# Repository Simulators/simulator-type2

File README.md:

# The Type 2 Liverpool Ringing Simulator

In this repository you will find all the resources for building the Liverpool Ringing Simulator Project's Type 2 simulator interfaces and sensor heads, including:
* Hardware & Software Manuals
* Firmware Source Code
* KiCad PCB Designs
* PCB Fabrication Gerber Files

You probably want to start in the docs folder above...

Please note that this is a Build-it-Yourself project. No pre-built hardware is available.

The original (Type 1) Liverpool Simulator hardware and code can be found in the legacy repository at https://github.com/Simulators/simulator. The Type 1 simulator is no longer under active development.

If you didn't get here from https://www.simulators.org.uk/, you might want to go and look at that, too.

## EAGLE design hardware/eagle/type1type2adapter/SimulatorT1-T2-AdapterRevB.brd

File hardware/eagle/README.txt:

*** DEPRECATED ***

These CAD files are the last to be produced using Eagle prior to migration of PCB development to KiCad. These are provided for reference only, and are no longer maintained.

Please use the KiCad CAD files where possible.

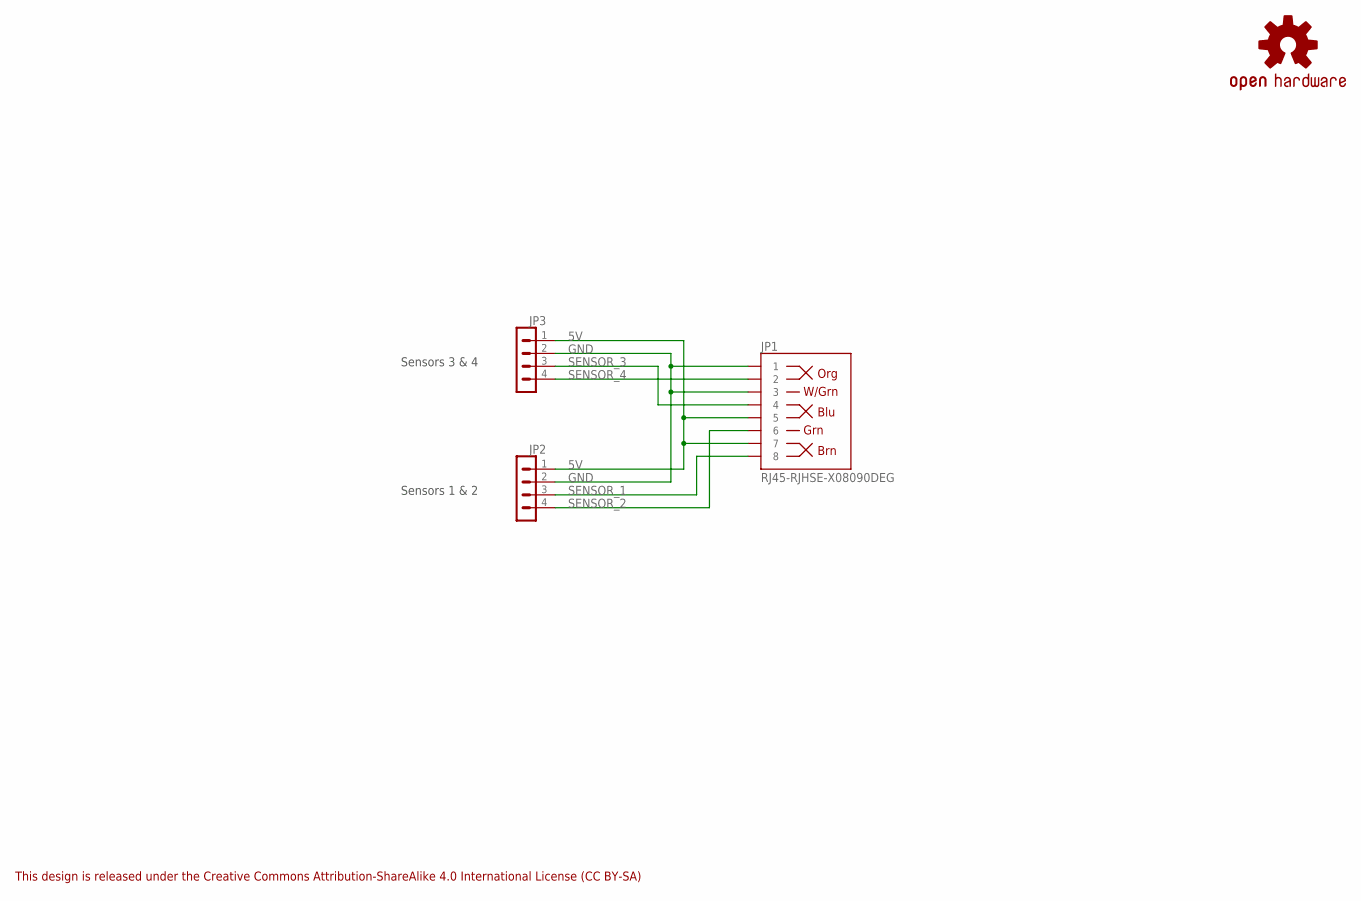
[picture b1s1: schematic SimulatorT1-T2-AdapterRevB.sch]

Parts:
JP1: RJ45-RJHSE-X08090DEG; RJ45-RJHSE-5080
JP2, JP3: MOLEX_KK_254_4WAY
LOGO1: OSHW-LOGOS; OSHW-LOGO-S

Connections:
5V: JP1.5, JP1.7, JP2.1, JP3.1
GND: JP1.1, JP1.3, JP2.2, JP3.2
SENSOR_1: JP1.8, JP2.3
SENSOR_2: JP1.6, JP2.4
SENSOR_3: JP1.4, JP3.3
SENSOR_4: JP1.2, JP3.4

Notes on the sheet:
This design is released under the Creative Commons Attribution-ShareAlike 4.0 International License (CC BY-SA)
Sensors 1 & 2
Sensors 3 & 4

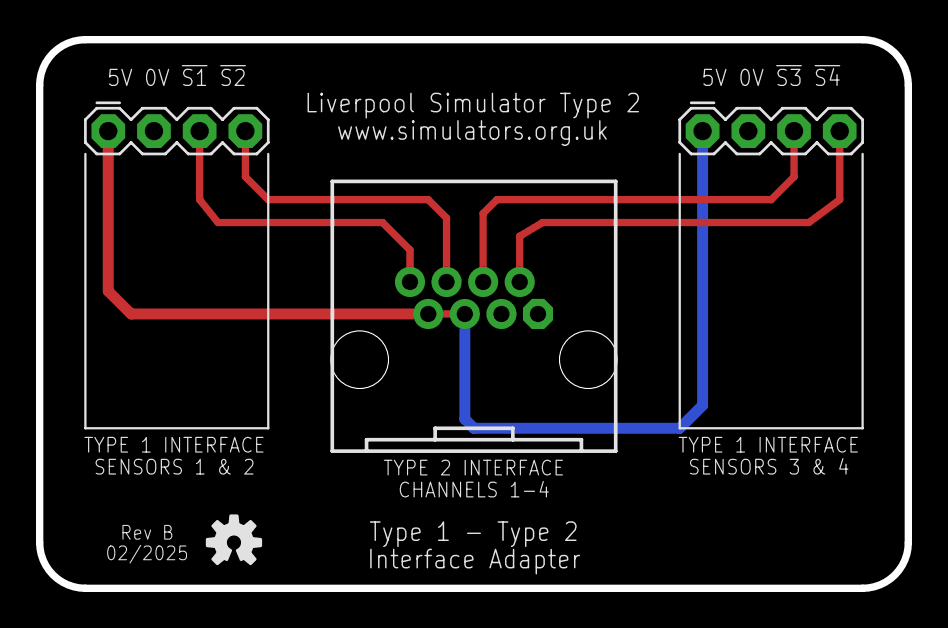
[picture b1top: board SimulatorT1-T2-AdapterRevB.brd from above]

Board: 2 copper layers, 48.3 x 30.5 mm, 5 parts (1 on the bottom side), 6 nets.

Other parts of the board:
U$1: WARNING_TRIANGLE_TPLACE

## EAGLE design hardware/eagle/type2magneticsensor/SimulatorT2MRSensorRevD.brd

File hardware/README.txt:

*** If you just want to order PCBs from a fabrication house, ready-made Gerber files can be found in the Gerbers directory ***

If you require PCB CAD files, please use those in the "kicad" subdirectory. The CAD files in the "eagle" subdirectory are the last to be produced using Eagle prior to migration of PCB development to KiCad. Those are provided for reference only, and are no longer maintained.

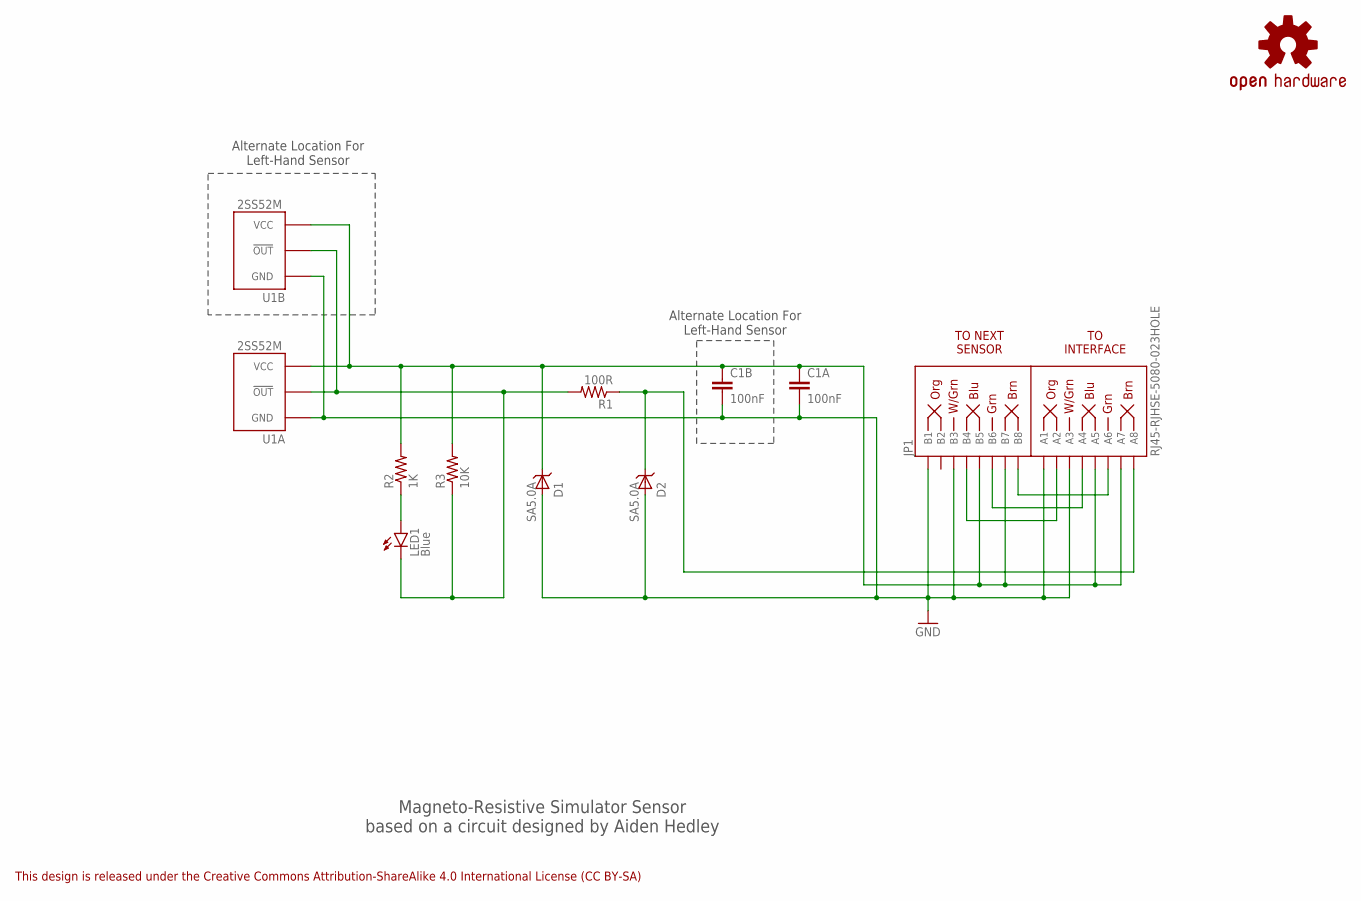
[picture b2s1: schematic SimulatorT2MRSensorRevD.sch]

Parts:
C1A, C1B: 100nF; CAP-PTH-SMALL
D1, D2: SA5.0A; DO41_TVS_UNI
JP1: RJ45-RJHSE-5080-023HOLE; RJ45-RJHSE-5080-02-3HOLE
LED1: Blue; LED3MM
LOGO1: OSHW-LOGOS; OSHW-LOGO-S
R1: 100R; AXIAL-0.4
R2: 1K; AXIAL-0.4
R3: 10K; AXIAL-0.4
U1A, U1B: 2SS52MOFFSET; 2SS52M_FLAT_OFFSET

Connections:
!OUT!: D2.CATHODE, JP1.A8, R1.P$1 (1)
B2: JP1.A6, JP1.B8
B3: JP1.A4, JP1.B6
B4: JP1.A2, JP1.B4
GND: C1A.2, C1B.2, D1.ANODE, D2.ANODE, JP1.A1, JP1.A3, JP1.B1, JP1.B3, U1A.P$1 (GND), U1B.P$1 (GND)
LED: LED1.A, R2.P$1 (1)
SIG: LED1.K (C), R1.P$2 (2), R3.P$1 (1), U1A.P$2 (!OUT!), U1B.P$2 (!OUT!)
VCC: C1A.1, C1B.1, D1.CATHODE, JP1.A5, JP1.A7, JP1.B5, JP1.B7, R2.P$2 (2), R3.P$2 (2), U1A.P$3 (VCC), U1B.P$3 (VCC)

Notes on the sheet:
This design is released under the Creative Commons Attribution-ShareAlike 4.0 International License (CC BY-SA)
TO INTERFACE
TO NEXT SENSOR
Magneto-Resistive Simulator Sensor based on a circuit designed by Aiden Hedley
Alternate Location For Left-Hand Sensor

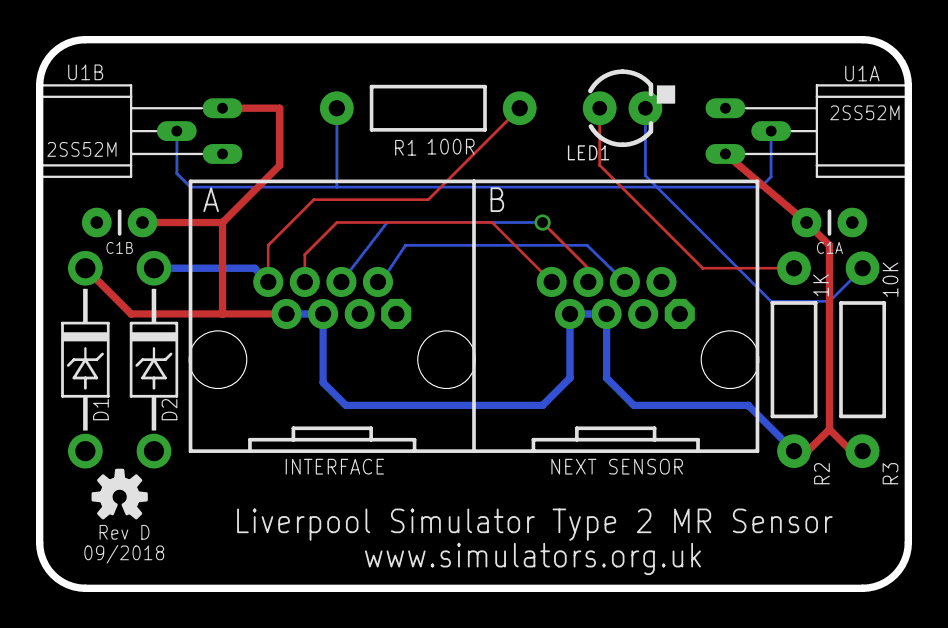
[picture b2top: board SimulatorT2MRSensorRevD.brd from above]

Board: 2 copper layers, 48.3 x 30.5 mm, 13 parts (1 on the bottom side), 8 nets.

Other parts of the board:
U$1: WARNING_TRIANGLE_TPLACE

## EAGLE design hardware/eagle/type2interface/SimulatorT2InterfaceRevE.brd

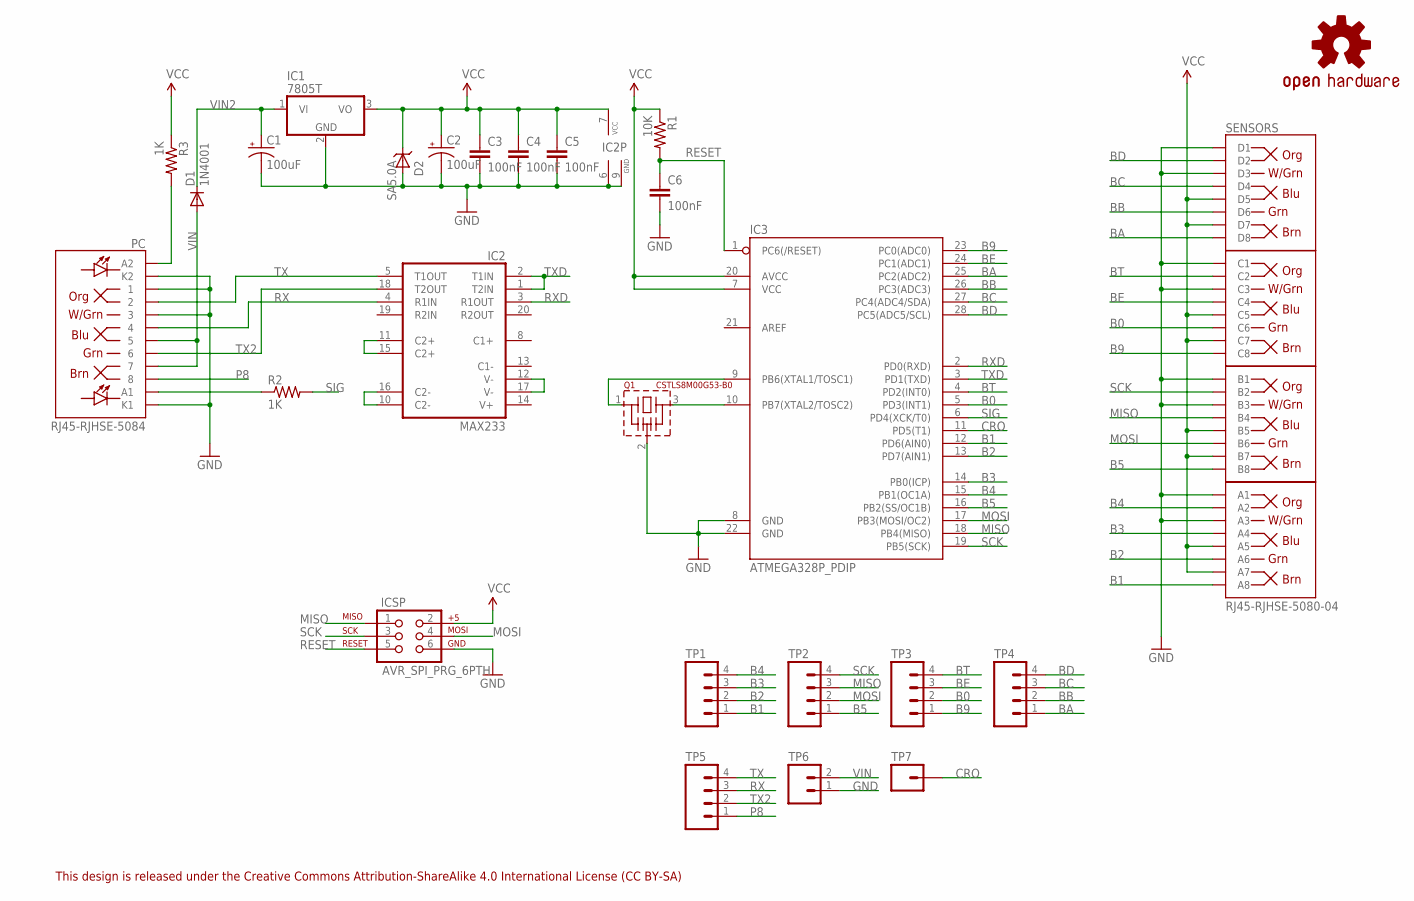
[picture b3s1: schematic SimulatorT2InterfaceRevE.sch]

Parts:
C1, C2: 100uF; CPOL-RADIAL-100UF-25V
C3, C4, C5, C6: 100nF; CAP-PTH-SMALL
D1: 1N4001; DO41_DIODE
D2: SA5.0A; DO41_TVS_UNI
IC1: 7805T; TO220H+TSR
IC2: MAX233; DIL20
IC3: ATMEGA328P_PDIP; DIL28-3
ICSP: AVR_SPI_PRG_6PTH; 2X3
LOGO1: OSHW-LOGOS; OSHW-LOGO-S
PC: RJ45-RJHSE-5084
Q1: CSTLS8M00G53-B0; CSTLS_G8
R1: 10K; AXIAL-0.4
R2, R3: 1K; AXIAL-0.4
SENSORS: RJ45-RJHSE-5080-04
TP1, TP2, TP3, TP4, TP5: M04PTH; 1X04
TP6: M02PTH; 1X02
TP7: M01PTH; 1X01

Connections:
B0: IC3.5 (PD3(INT1)), SENSORS.C6, TP3.2
B1: IC3.12 (PD6(AIN0)), SENSORS.A8, TP1.1
B2: IC3.13 (PD7(AIN1)), SENSORS.A6, TP1.2
B3: IC3.14 (PB0(ICP)), SENSORS.A4, TP1.3
B4: IC3.15 (PB1(OC1A)), SENSORS.A2, TP1.4
B5: IC3.16 (PB2(SS/OC1B)), SENSORS.B8, TP2.1
B9: IC3.23 (PC0(ADC0)), SENSORS.C8, TP3.1
BA: IC3.25 (PC2(ADC2)), SENSORS.D8, TP4.1
BB: IC3.26 (PC3(ADC3)), SENSORS.D6, TP4.2
BC: IC3.27 (PC4(ADC4/SDA)), SENSORS.D4, TP4.3
BD: IC3.28 (PC5(ADC5/SCL)), SENSORS.D2, TP4.4
BE: IC3.24 (PC1(ADC1)), SENSORS.C4, TP3.3
BT: IC3.4 (PD2(INT0)), SENSORS.C2, TP3.4
CRO: IC3.11 (PD5(T1)), TP7.1
GND: C1.2 (-), C2.2 (-), C3.2, C4.2, C5.2, C6.2, D2.ANODE, IC1.2 (GND), IC2.6 (GND), IC2.9 (GND), IC3.8 (GND), IC3.22 (GND), ICSP.6, PC.1, PC.3, PC.K1, PC.K2, Q1.2 (GND), SENSORS.A1, SENSORS.A3, SENSORS.B1, SENSORS.B3, SENSORS.C1, SENSORS.C3, SENSORS.D1, SENSORS.D3, TP6.1
LED1: PC.A1, R2.P$1 (1)
LED2: PC.A2, R3.P$2 (2)
MISO: IC3.18 (PB4(MISO)), ICSP.1, SENSORS.B4, TP2.3
MOSI: IC3.17 (PB3(MOSI/OC2)), ICSP.4, SENSORS.B6, TP2.2
unnamed: IC2.10 (C2-), IC2.16 (C2-)
unnamed: IC2.11 (C2+), IC2.15 (C2+)
unnamed: IC2.12 (V-), IC2.17 (V-)
OSC1: IC3.9 (PB6(XTAL1/TOSC1)), Q1.1
OSC2: IC3.10 (PB7(XTAL2/TOSC2)), Q1.3
P8: PC.8, TP5.1
RESET: C6.1, IC3.1 (PC6(/RESET)), ICSP.5, R1.P$2 (2)
RX: IC2.4 (R1IN), PC.4, TP5.3
RXD: IC2.3 (R1OUT), IC3.2 (PD0(RXD))
SCK: IC3.19 (PB5(SCK)), ICSP.3, SENSORS.B2, TP2.4
SIG: IC3.6 (PD4(XCK/T0)), R2.P$2 (2)
TX: IC2.5 (T1OUT), PC.2, TP5.4
TX2: IC2.18 (T2OUT), PC.6, TP5.2
TXD: IC2.1 (T2IN), IC2.2 (T1IN), IC3.3 (PD1(TXD))
VCC: C2.1 (+), C3.1, C4.1, C5.1, D2.CATHODE, IC1.3 (VO), IC2.7 (VCC), IC3.7 (VCC), IC3.20 (AVCC), ICSP.2, R1.P$1 (1), R3.P$1 (1), SENSORS.A5, SENSORS.A7, SENSORS.B5, SENSORS.B7, SENSORS.C5, SENSORS.C7, SENSORS.D5, SENSORS.D7
VIN: D1.A, PC.5, PC.7, TP6.2
VIN2: C1.1 (+), D1.C, IC1.1 (VI)

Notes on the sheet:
This design is released under the Creative Commons Attribution-ShareAlike 4.0 International License (CC BY-SA)

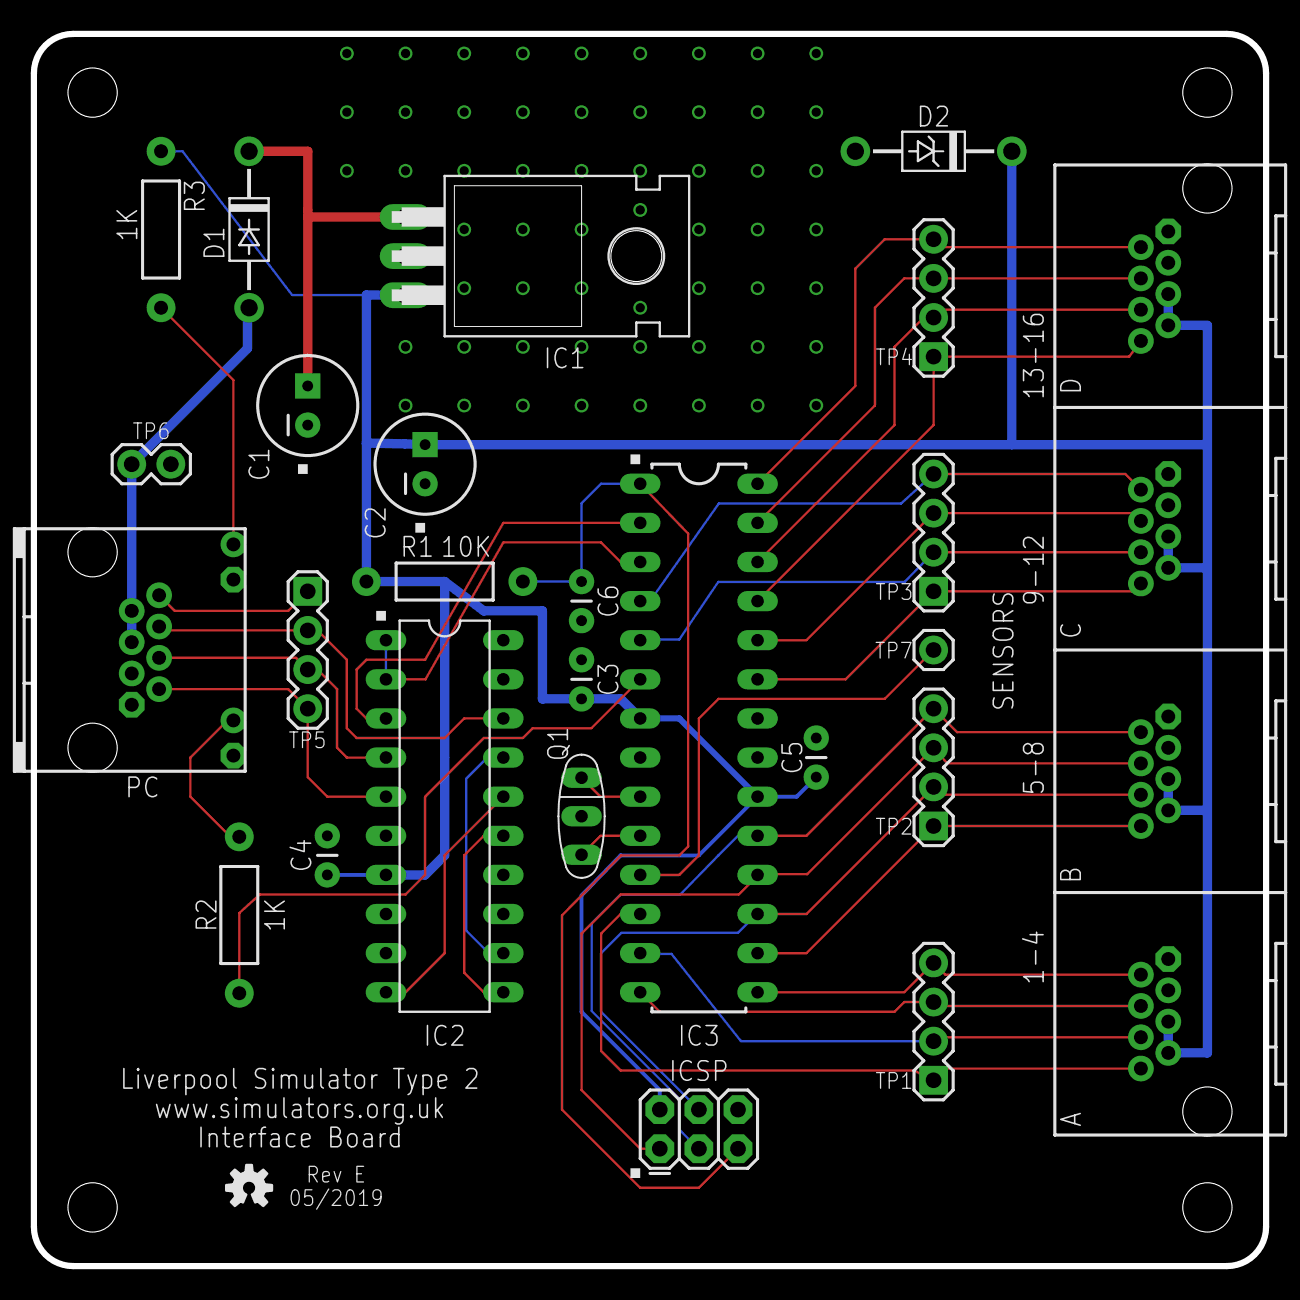
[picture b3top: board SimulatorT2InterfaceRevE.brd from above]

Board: 2 copper layers, 80.0 x 80.0 mm, 27 parts (1 on the bottom side), 36 nets.

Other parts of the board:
U$1: WARNING_TRIANGLE_TPLACE

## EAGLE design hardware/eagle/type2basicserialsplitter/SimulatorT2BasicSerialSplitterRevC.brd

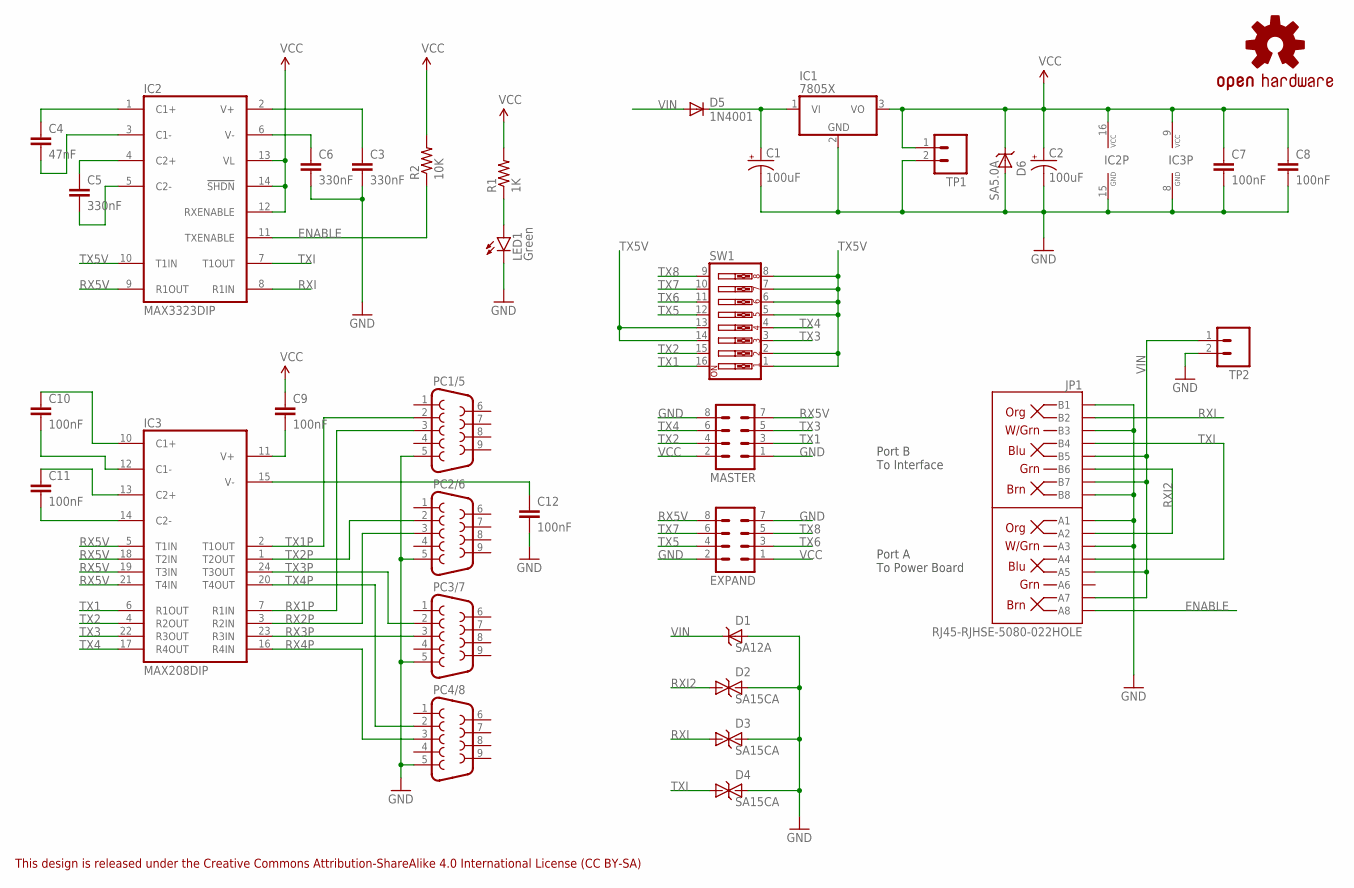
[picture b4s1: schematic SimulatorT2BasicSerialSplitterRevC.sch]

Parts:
C1, C2: 100uF; CPOL-RADIAL-100UF-25V
C3, C5, C6: 330nF; CAP-PTH-SMALL
C4: 47nF; CAP-PTH-SMALL
C7, C8, C9, C10, C11, C12: 100nF; CAP-PTH-SMALL
D1: SA12A; DO41_TVS_UNI
D2, D3, D4: SA15CA; DO41_TVS_BI
D5: 1N4001; DO41_DIODE
D6: SA5.0A; DO41_TVS_UNI
EXPAND: M04X2POL; 2X4-POLARISED
IC1: 7805X; TO220H
IC2: MAX3323DIP; DIL16
IC3: MAX208DIP; DIL24
JP1: RJ45-RJHSE-5080-022HOLE; RJ45-RJHSE-5080-02
LED1: Green; LED3MM_LARGEHOLES
LOGO1: OSHW-LOGOS; OSHW-LOGO-S
MASTER: M04X2POL; 2X4-POLARISED
PC1/5, PC2/6, PC3/7, PC4/8: DB9-CONNECTOR-PCBFEMALE; MULTICOMP-DB9-FEMALE-PCB-90DEG
R1: 1K; AXIAL-0.4
R2: 10K; AXIAL-0.4
SW1: SW_DIP-8; DIPSWITCH-08
TP1, TP2: M02PTH; 1X02

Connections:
ENABLE: IC2.11 (TXENABLE), JP1.A8, R2.P$1 (1)
GND: C1.2 (-), C2.2 (-), C3.2, C6.2, C7.2, C8.2, C12.2, D1.ANODE, D2.C, D3.C, D4.C, D6.ANODE, EXPAND.2, EXPAND.7, IC1.2 (GND), IC2.15 (GND), IC3.8 (GND), JP1.A1, JP1.A3, JP1.B1, JP1.B3, JP1.B8, LED1.K (C), MASTER.1, MASTER.8, PC1/5.5, PC2/6.5, PC3/7.5, PC4/8.5, TP1.2, TP2.2
unnamed: C3.1, IC2.2 (V+)
unnamed: C6.1, IC2.6 (V-)
unnamed: C5.1, IC2.4 (C2+)
unnamed: C5.2, IC2.5 (C2-)
unnamed: C4.1, IC2.1 (C1+)
unnamed: C4.2, IC2.3 (C1-)
unnamed: C11.2, IC3.14 (C2-)
unnamed: C11.1, IC3.13 (C2+)
unnamed: C10.1, IC3.10 (C1+)
unnamed: C10.2, IC3.12 (C1-)
unnamed: C12.1, IC3.15 (V-)
unnamed: C9.2, IC3.11 (V+)
POWER_LED: LED1.A, R1.P$1 (1)
RX1P: IC3.7 (R1IN), PC1/5.3
RX2P: IC3.3 (R2IN), PC2/6.3
RX3P: IC3.23 (R3IN), PC3/7.3
RX4P: IC3.16 (R4IN), PC4/8.3
RX5V: EXPAND.8, IC2.9 (R1OUT), IC3.5 (T1IN), IC3.18 (T2IN), IC3.19 (T3IN), IC3.21 (T4IN), MASTER.7
RXI: D3.A, IC2.8 (R1IN), JP1.B2
RXI2: D2.A, JP1.A2, JP1.B6
TX1: IC3.6 (R1OUT), MASTER.3, SW1.16
TX1P: IC3.2 (T1OUT), PC1/5.2
TX2: IC3.4 (R2OUT), MASTER.4, SW1.15
TX2P: IC3.1 (T2OUT), PC2/6.2
TX3: IC3.22 (R3OUT), MASTER.5, SW1.3
TX3P: IC3.24 (T3OUT), PC3/7.2
TX4: IC3.17 (R4OUT), MASTER.6, SW1.4
TX4P: IC3.20 (T4OUT), PC4/8.2
TX5: EXPAND.4, SW1.12
TX5V: IC2.10 (T1IN), SW1.1, SW1.2, SW1.5, SW1.6, SW1.7, SW1.8, SW1.13, SW1.14
TX6: EXPAND.3, SW1.11
TX7: EXPAND.6, SW1.10
TX8: EXPAND.5, SW1.9
TXI: D4.A, IC2.7 (T1OUT), JP1.A4, JP1.B4
VCC: C2.1 (+), C7.1, C8.1, C9.1, D6.CATHODE, EXPAND.1, IC1.3 (VO), IC2.12 (RXENABLE), IC2.13 (VL), IC2.14 (!SHDN), IC2.16 (VCC), IC3.9 (VCC), MASTER.2, R1.P$2 (2), R2.P$2 (2), TP1.1
VIN: D1.CATHODE, D5.A, JP1.A5, JP1.A7, JP1.B5, JP1.B7, TP2.1
VREG_IN: C1.1 (+), D5.C, IC1.1 (VI)

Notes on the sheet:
This design is released under the Creative Commons Attribution-ShareAlike 4.0 International License (CC BY-SA)
Port A To Power Board
Port B To Interface

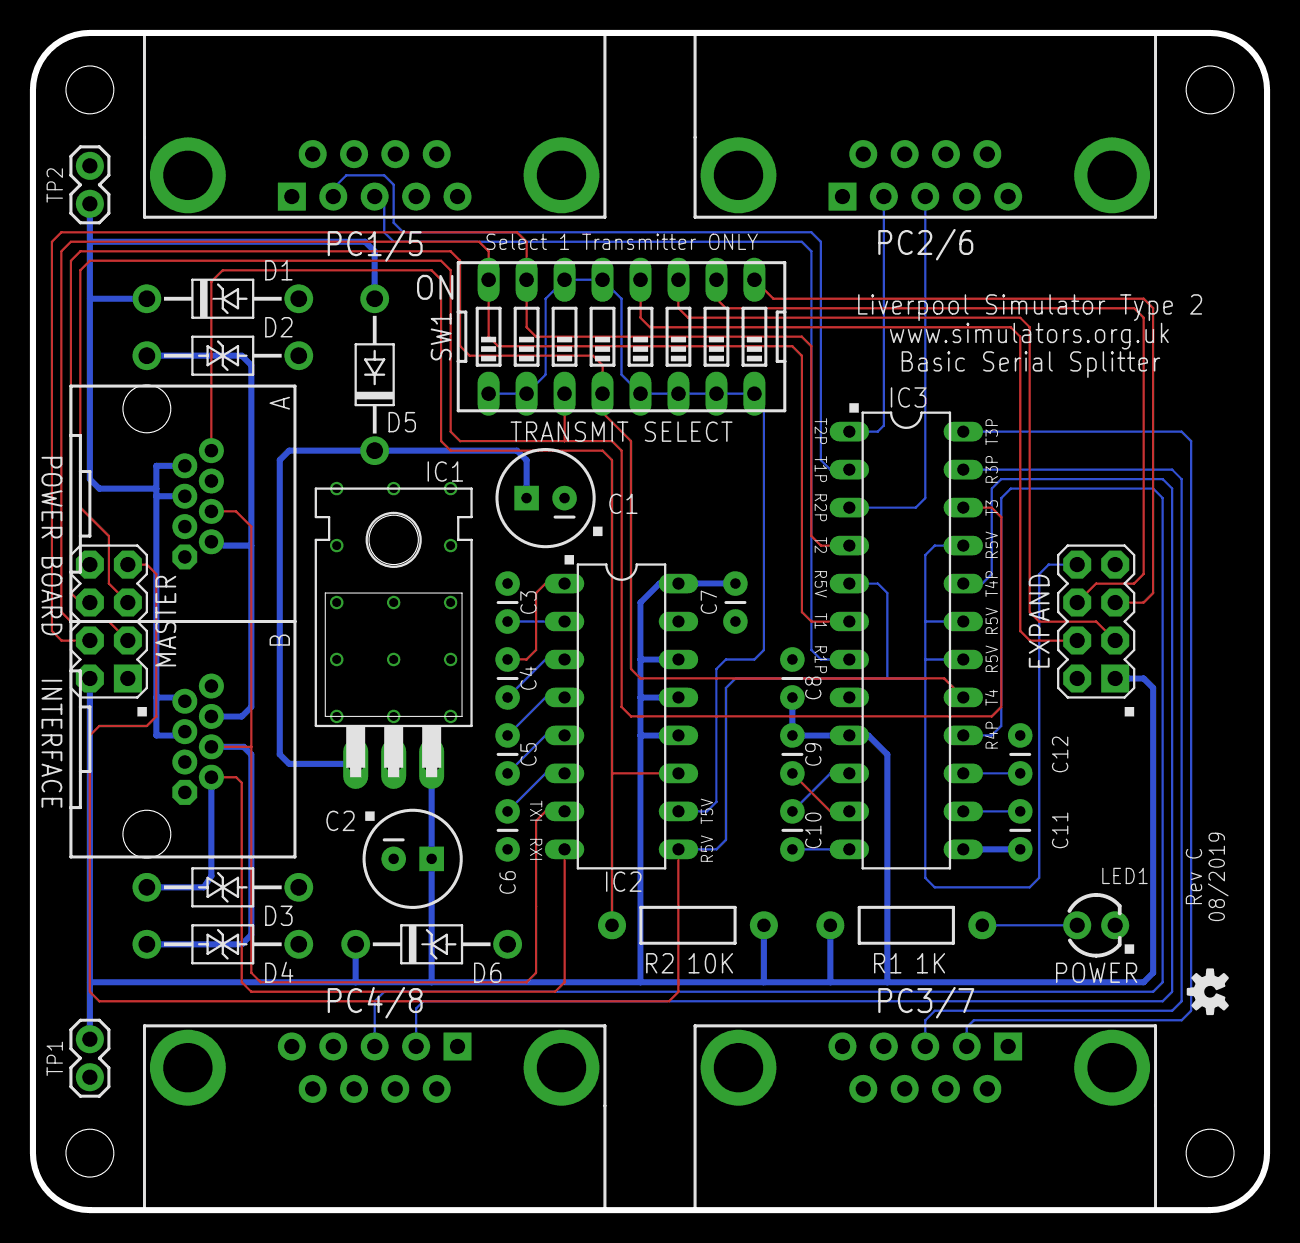
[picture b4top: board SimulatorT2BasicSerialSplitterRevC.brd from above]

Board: 2 copper layers, 82.5 x 78.7 mm, 36 parts (1 on the bottom side), 39 nets.

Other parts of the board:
U$1: WARNING_TRIANGLE_TPLACE

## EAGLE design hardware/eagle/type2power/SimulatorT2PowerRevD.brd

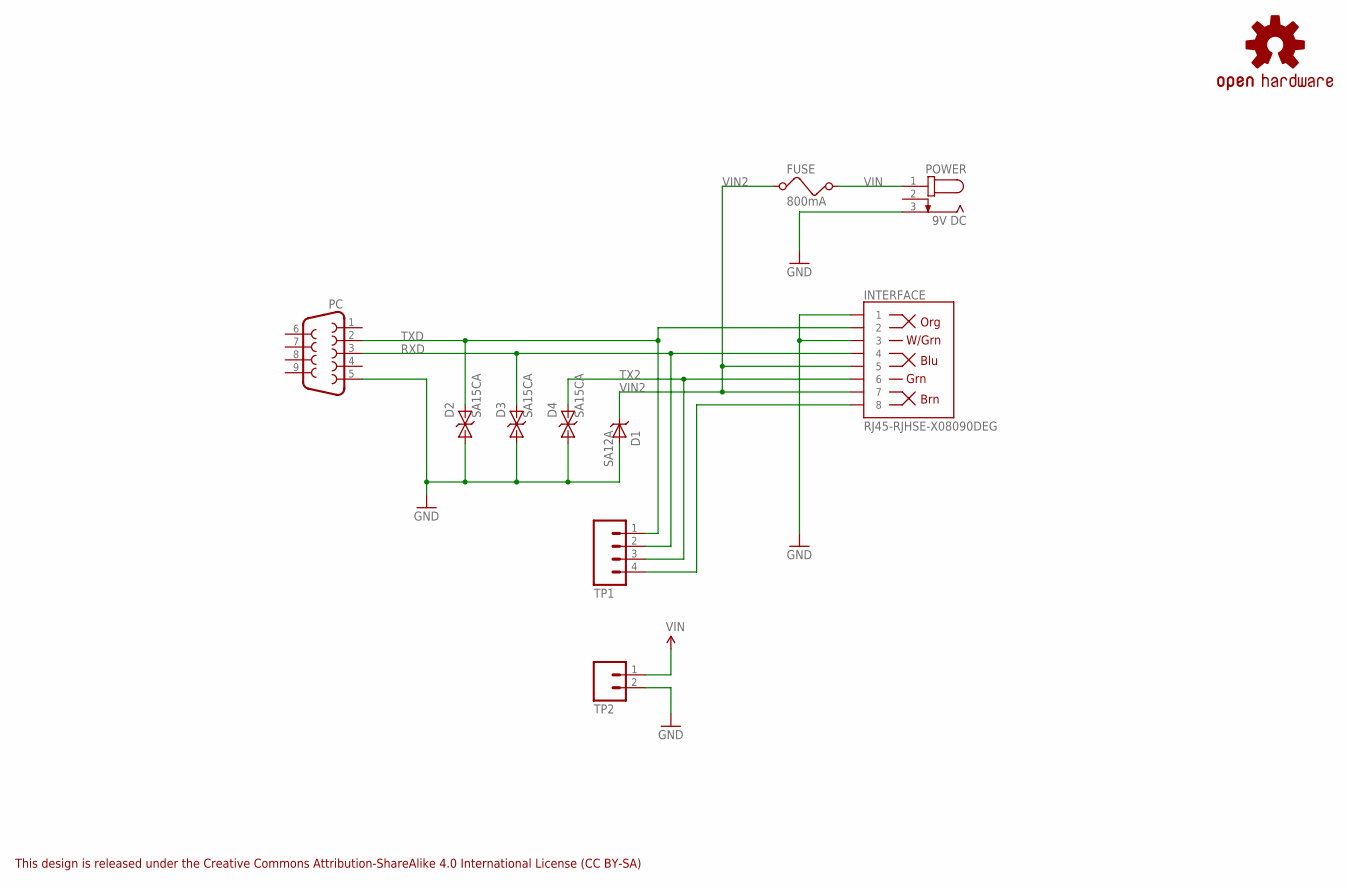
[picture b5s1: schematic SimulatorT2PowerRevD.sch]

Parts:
D1: SA12A; DO41_TVS_UNI
D2, D3, D4: SA15CA; DO41_TVS_BI
FUSE: 800mA; MCOMP-FUSE-HOLDER-PCB
INTERFACE: RJ45-RJHSE-X08090DEG; RJ45-RJHSE-5080
LOGO1: OSHW-LOGOS; OSHW-LOGO-S
PC: DB9-CONNECTOR-PCBFEMALE; MULTICOMP-DB9-FEMALE-PCB-90DEG
POWER: 9V DC; CLIFF-FC681465P-DC-JACK
TP1: M04PTH; 1X04
TP2: M02PTH; 1X02

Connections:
GND: D1.ANODE, D2.A, D3.A, D4.A, INTERFACE.1, INTERFACE.3, PC.5, POWER.3, TP2.2
P8: INTERFACE.8, TP1.4
RXD: D3.C, INTERFACE.4, PC.3, TP1.2
TX2: D4.C, INTERFACE.6, TP1.3
TXD: D2.C, INTERFACE.2, PC.2, TP1.1
VIN: FUSE.2, POWER.1, TP2.1
VIN2: D1.CATHODE, FUSE.1, INTERFACE.5, INTERFACE.7

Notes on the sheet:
This design is released under the Creative Commons Attribution-ShareAlike 4.0 International License (CC BY-SA)

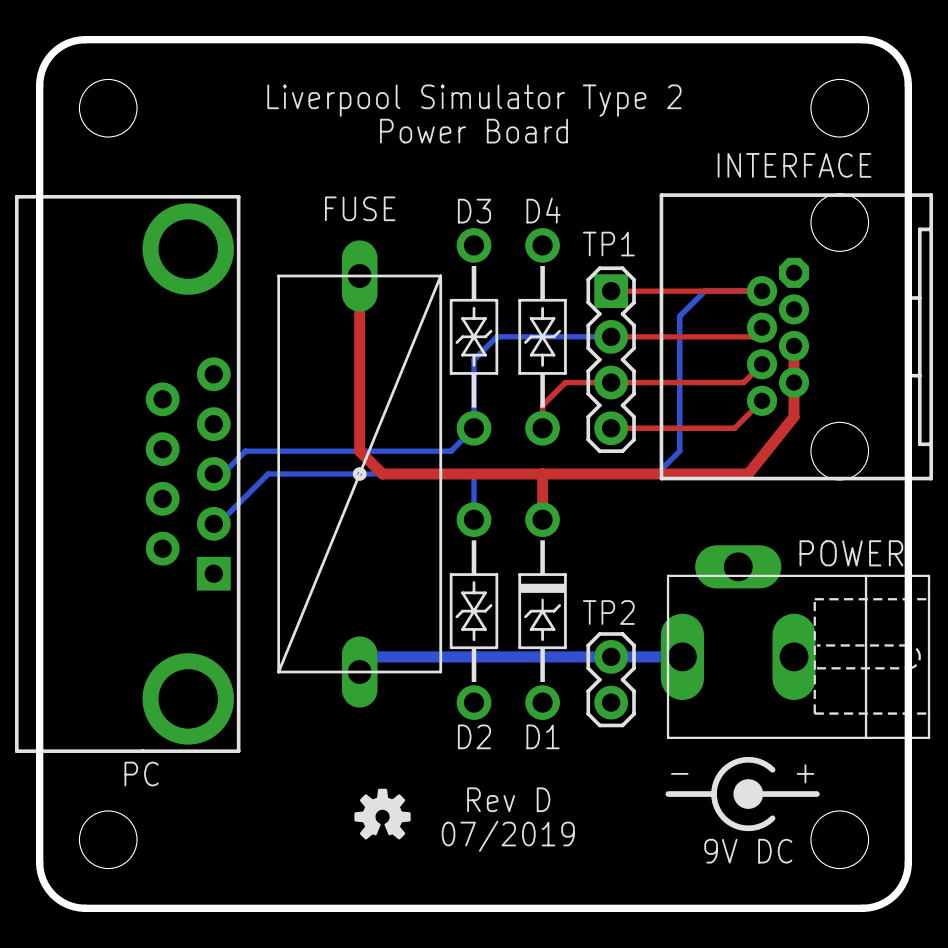
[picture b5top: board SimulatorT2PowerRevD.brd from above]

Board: 2 copper layers, 48.3 x 48.3 mm, 12 parts (0 on the bottom side), 7 nets.

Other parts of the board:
U$1: CENTRE-POS-SILK

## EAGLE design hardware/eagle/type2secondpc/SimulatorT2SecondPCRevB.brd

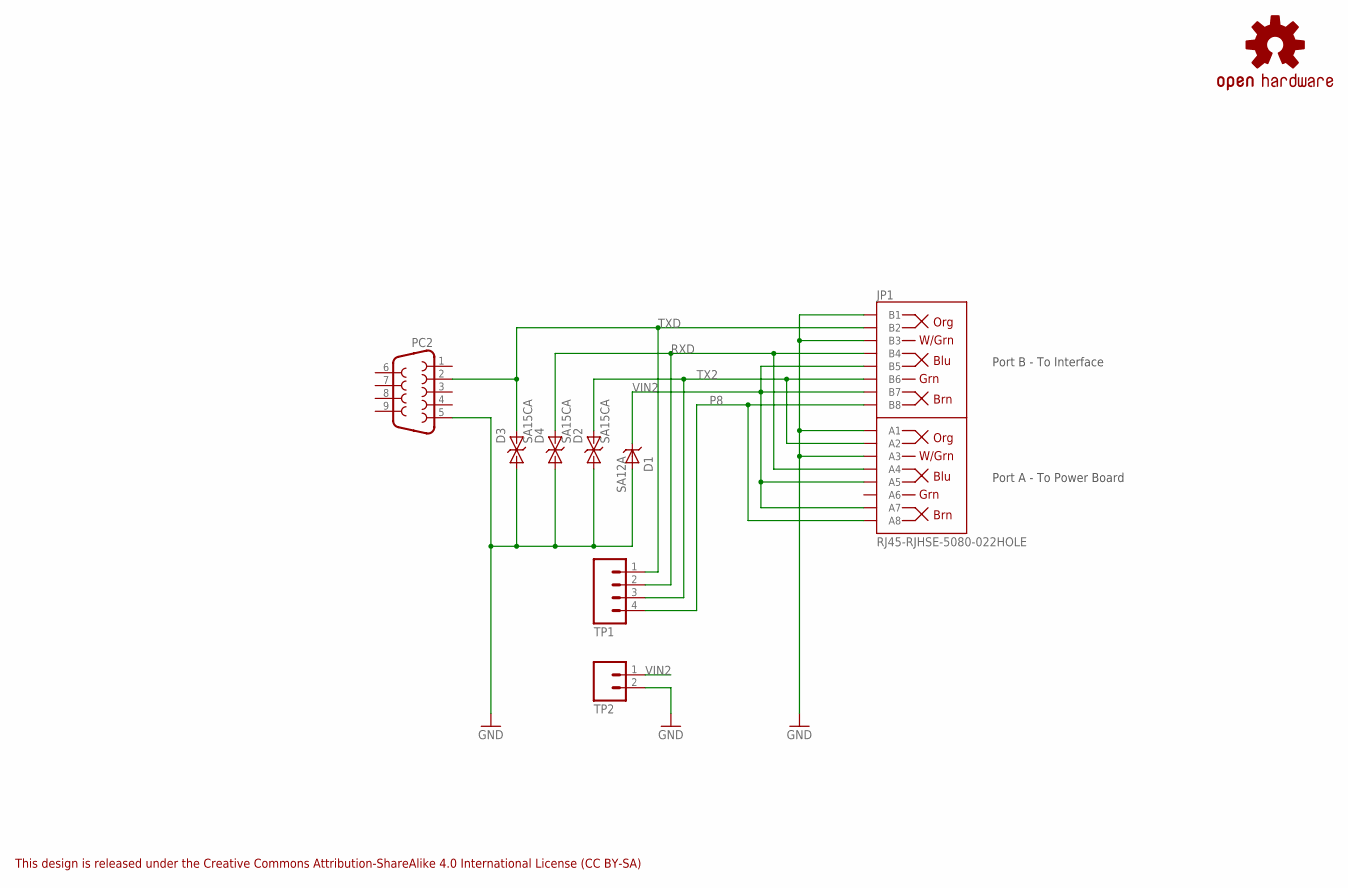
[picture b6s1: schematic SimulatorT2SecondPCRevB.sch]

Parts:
D1: SA12A; DO41_TVS_UNI
D2, D3, D4: SA15CA; DO41_TVS_BI
JP1: RJ45-RJHSE-5080-022HOLE; RJ45-RJHSE-5080-02
LOGO1: OSHW-LOGOS; OSHW-LOGO-S
PC2: DB9-CONNECTOR-PCBFEMALE; MULTICOMP-DB9-FEMALE-PCB-90DEG
TP1: M04PTH; 1X04
TP2: M02PTH; 1X02

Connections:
GND: D1.ANODE, D2.A, D3.A, D4.A, JP1.A1, JP1.A3, JP1.B1, JP1.B3, PC2.5, TP2.2
P8: JP1.A8, JP1.B8, TP1.4
RXD: D4.C, JP1.A4, JP1.B4, TP1.2
TX2: D2.C, JP1.A2, JP1.B6, TP1.3
TXD: D3.C, JP1.B2, PC2.2, TP1.1
VIN2: D1.CATHODE, JP1.A5, JP1.A7, JP1.B5, JP1.B7, TP2.1

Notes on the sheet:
This design is released under the Creative Commons Attribution-ShareAlike 4.0 International License (CC BY-SA)
Port B - To Interface
Port A - To Power Board

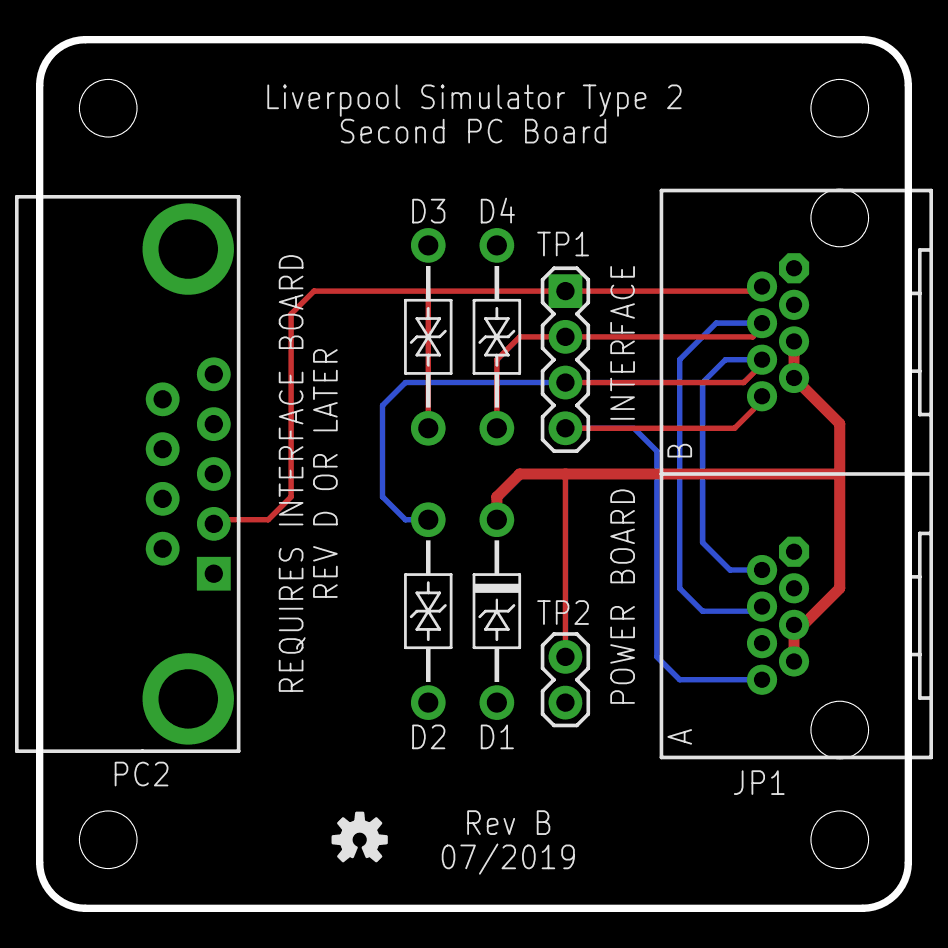
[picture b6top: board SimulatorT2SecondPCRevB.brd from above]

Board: 2 copper layers, 48.3 x 48.3 mm, 9 parts (0 on the bottom side), 6 nets.

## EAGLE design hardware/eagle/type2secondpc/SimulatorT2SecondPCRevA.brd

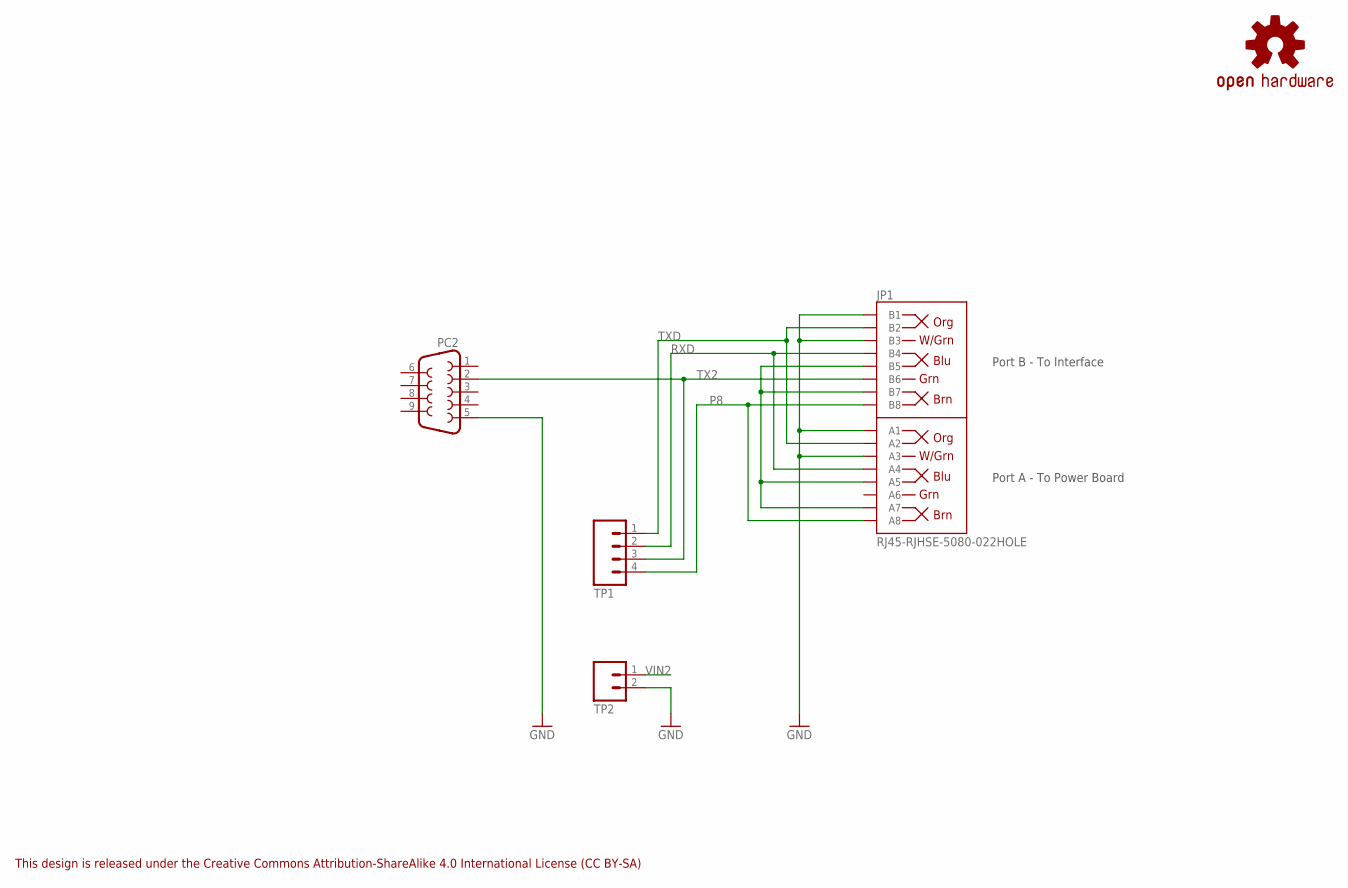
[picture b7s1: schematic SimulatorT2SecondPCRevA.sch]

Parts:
JP1: RJ45-RJHSE-5080-022HOLE; RJ45-RJHSE-5080-02
LOGO1: OSHW-LOGOS; OSHW-LOGO-S
PC2: DB9-CONNECTOR-PCBFEMALE; MULTICOMP-DB9-FEMALE-PCB-90DEG
TP1: M04PTH; 1X04
TP2: M02PTH; 1X02

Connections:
GND: JP1.A1, JP1.A3, JP1.B1, JP1.B3, PC2.5, TP2.2
P8: JP1.A8, JP1.B8, TP1.4
RXD: JP1.A4, JP1.B4, TP1.2
TX2: JP1.B6, PC2.2, TP1.3
TXD: JP1.A2, JP1.B2, TP1.1
VIN2: JP1.A5, JP1.A7, JP1.B5, JP1.B7, TP2.1

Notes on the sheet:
This design is released under the Creative Commons Attribution-ShareAlike 4.0 International License (CC BY-SA)
Port B - To Interface
Port A - To Power Board

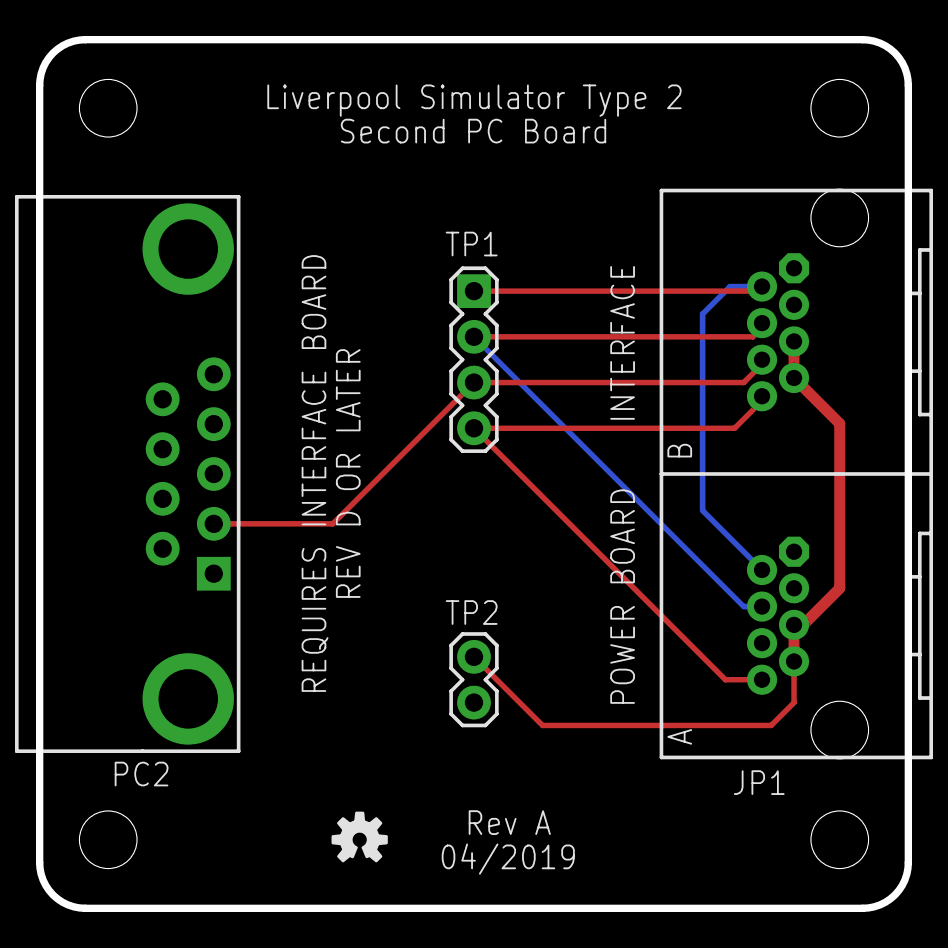
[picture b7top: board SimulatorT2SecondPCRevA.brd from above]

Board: 2 copper layers, 48.3 x 48.3 mm, 5 parts (0 on the bottom side), 6 nets.

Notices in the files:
parts and their libraries:
SparkFun-Aesthetics: Licensing: Creative Commons ShareAlike 4.0 International - https://creativecommons.org/licenses/by-sa/4.0
